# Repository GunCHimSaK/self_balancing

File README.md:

# FOC 정밀 제어 기반 자율주행 밸런싱 로봇

BLDC 모터 2개로 균형을 잡는 2륜 셀프 밸런싱 로봇입니다. 이전 프로젝트([라즈베리파이 자율주행 버스](https://github.com/GunCHimSaK/raspi-autonomous-car))의 차선 인식 주행을 이 로봇에 옮기는 것을 목표로 합니다.
모터는 FOC(Field-Oriented Control)로 토크를 직접 제어해서, DC 모터보다 부드럽고 정밀하게 움직입니다.

- **MCU**: STM32 NUCLEO-F446RE (PlatformIO + Arduino 프레임워크). 처음에는 NUCLEO-F103RB로 시작했습니다.
- **IMU**: BNO055 (MPU6050에서 교체)
- **상위 제어기**: Raspberry Pi 4B (카메라 비전, 주행 명령)
- **통신**: CAN (Raspberry Pi MCP2515 HAT ↔ STM32 TJA1050)
- **기간**: 2025.06 ~ 2026.02

## 시스템 구조

```
[Raspberry Pi 4B]  카메라 → 차선 인식 → throttle / steer
        │  CAN 500kbps (MCP2515 HAT ↔ TJA1050), ID 0x100
        ▼
[STM32 NUCLEO-F446RE]
   BNO055 (I2C1) ──▶ 현재 기울기 ──────────────┐
   AS5048A ×2 (SPI1/SPI2) ──▶ 바퀴 속도 ──▶ 속도 PID ──▶ 목표 기울기
                                               ▼
                                     기울기 PID ──▶ 토크 명령 ± steering
                                               ▼
                               SimpleFOC 토크 제어 (FOC)
        ├─ SimpleFOC Shield A → GM4108 모터 A
        └─ SimpleFOC Shield B → GM4108 모터 B
```

## 제어 구조

**1. FOC 토크 제어 (SimpleFOC)**
- 모터: GM4108 (11 pole pairs), 전원 설정 10V
- 제어 모드: `MotionControlType::torque` (전압 기반 토크 제어)
- 회전자 각도: AS5048A 14bit 자기 엔코더 (SPI 500kHz, 저수준 직접 읽기)

**2. 캐스케이드 밸런싱 제어** (`src/main.cpp`)

```
바퀴 평균 속도 = (모터1 속도 + 모터2 속도) / 2
목표 기울기 = LPF( pid_vel(바퀴 평균 속도 − LPF(throttle)) ) + 0.045      ← 바깥 루프 (속도)
토크 명령   = −pid_stb(목표 기울기 − 현재 기울기)                         ← 안쪽 루프 (기울기)
모터1 = 토크 명령 + LPF(steering),  모터2 = 토크 명령 − LPF(steering)
```

| 제어기 | P | I | D | 출력 제한 |
|---|---|---|---|---|
| `pid_stb` (기울기 → 토크) | 30 | 100 | 1 | 8V |
| `pid_vel` (속도 → 목표 기울기) | 0.01 | 0.03 | 0 | π/10 rad |

- 속도 루프가 로봇이 한쪽으로 굴러가는 것을 막고, `throttle`을 주면 그 속도로 움직입니다.
- `+0.045 rad`는 무게중심이 치우친 만큼의 보정값입니다.
- 시리얼 Commander로 PID 실시간 튜닝 (`A` = 기울기 PID, `B` = 속도 PID)

**3. 자세 추정 (BNO055)**
- 칩 안에서 9축 센서 퓨전을 하는 BNO055의 Euler pitch 레지스터(`0x1E`)를 2바이트 직접 읽습니다 (1° = 16 LSB).
- I2C1(PB8/PB9) 400kHz

| 버전 | 방식 | 결과 |
|---|---|---|
| MPU6050 + 상보 필터 | 레지스터 직접 읽기(burst read) + 가속도 LPF + 상보 필터 | 급격한 기울기에서 멈춤 |
| MPU6050 DMP | DMP 쿼터니언으로 pitch 계산 | 튜닝 성공, 그러나 한 방향 drift |
| **BNO055** | 9축 센서 퓨전 결과 직접 읽기 | drift 해결 (최종) |

**4. CAN 통신** (단독 테스트 완료, 밸런싱 코드와 통합 예정)
- STM32 CAN을 HAL로 직접 초기화한 수신 테스트 (500kbps, F103RB)
- 메시지 `0x100`: `throttle×1000`, `steer×1000`을 big-endian int16 2개로 전송

코드가 단계별로 어떻게 바뀌었는지는 [docs/DEVELOPMENT_LOG.md](docs/DEVELOPMENT_LOG.md)에 정리했습니다.

## 폴더 구조

```
├── src/main.cpp                  밸런싱 메인 펌웨어 (최종: F446RE, BNO055, 캐스케이드 PID)
├── lib/MySensors/
│   ├── balancer_pinouts.h        핀 정의
│   ├── CustomAS5048A.*           AS5048A SPI 저수준 드라이버 (SimpleFOC Sensor 상속)
│   ├── MPU6050_Handler.*         MPU6050 레지스터 + 상보 필터
│   └── mpu6050v2.*               MPU6050 DMP
├── versions/                     단계별 이전 코드 (v1 MPU6050, v2 CAN 수신, v3 BNO055)
├── raspberry_pi/can_sender.py    라즈베리파이 CAN 송신 테스트 (python-can)
├── hardware/
│   ├── cubemx/                   핀 할당 전용 CubeMX 파일 (F446RE, F103RB)
│   └── interface_pcb/            전원·버튼 인터페이스 PCB (KiCad, 거버, BOM)
├── docs/PINMAP.md                전체 핀맵과 핀 충돌 정리
├── docs/DEVELOPMENT_LOG.md       단계별 코드 변화 기록
└── platformio.ini
```

## 핀맵 요약

| 기능 | 모터 A | 모터 B |
|---|---|---|
| 엔코더 SPI (SCK/MISO/MOSI/CS) | SPI1: PA5 / PA6 / PA7 / PB5 | SPI2: PB13 / PB14 / PB15 / PB2 |
| PWM A/B/C상 | PB10 (TIM2) / PB6 (TIM4) / PB4 (TIM3) | PA8 / PA9 / PA10 (TIM1) |
| Enable | PC7 | PA11 (`.ioc`에서는 PC8) |

| 기능 | 핀 |
|---|---|
| I2C1 (BNO055, LCD) | PB8 SCL / PB9 SDA |
| CAN | PA11 RX / PA12 TX (`.ioc` 기준) |
| 디버그 UART | PA2 / PA3 (USART2, ST-LINK) |

자세한 내용과 핀 충돌 정리는 [docs/PINMAP.md](docs/PINMAP.md)에 있습니다.

## 빌드

```bash
pio run -t upload          # 밸런싱 펌웨어 업로드
pio device monitor         # 115200bps, Commander로 PID 튜닝
```
CAN 수신 테스트는 `versions/v2_can_receiver_hal_f103rb.cpp`를 `src/main.cpp`로 바꾸고, `platformio.ini`의 보드를 `nucleo_f103rb`로 바꿔 빌드합니다.
라즈베리파이 쪽은 `sudo ip link set can0 up type can bitrate 500000` 후 `python3 raspberry_pi/can_sender.py`를 실행합니다.

## 개발 중 문제와 해결

| 문제 | 원인 | 해결 |
|---|---|---|
| SimpleFOC에서 AS5048A 값이 안 읽힘 | 원인을 찾지 못함 (라이브러리 기본 SPI 센서 클래스 문제로 추정) | SPI를 직접 읽는 `CustomAS5048A` 클래스를 만들어 SimpleFOC `Sensor`로 연결 |
| 모터 2개를 동시에 못 돌림 | 두 쉴드의 PWM 핀이 같은 타이머를 사용 | PWM 선을 끊고 타이머가 겹치지 않는 핀(모터 B → TIM1)으로 다시 납땜 |
| 모터 1개 고장 | 모터 규격보다 긴 나사가 내부 코일을 끊음 | 모터 교체, 나사 길이 확인 |
| 급격히 기울이면 로봇이 멈춤 | IMU 통신 중 멈춤 | burst read로 I2C 통신 횟수를 줄이고, DMP 방식으로 변경 |
| 각도가 한 방향으로 흘러감 (drift) | 6축 센서 한계 또는 센서 불량 | BNO055 9축 센서로 교체 |
| 엔코더 값 불안정 | SPI 속도와 CS 타이밍 | SPI 1MHz → 500kHz, CS를 내린 뒤 1µs 대기 |
| 제자리에 서지 못하고 굴러감 | 기울기만 제어 | 바퀴 속도 루프를 바깥에 둔 캐스케이드 PID |
| 디커플링 커패시터가 제 역할을 못 함 (PCB) | 100µF 커패시터를 전원–GND 사이가 아니라 12V 라인에 직렬로 배치 | 2차 설계에서 전원–GND 사이, IC 핀 가까이 배치 |
| 센서·버튼 입력값이 튐 (PCB) | 커넥터에 GND 핀이 없어 기준 전위가 공유되지 않음 | GND 선을 따로 연결, 2차 설계에서 모든 신호 커넥터에 GND 핀 추가 |
| CAN과 IMU 핀 충돌 | CAN remap(PB8/PB9)과 I2C1 핀이 같음 | CAN을 PA11/PA12로 옮기는 핀 배치 정리 (`.ioc`) |

## 사용 도구
STM32CubeMX · PlatformIO · VS Code · SimpleFOC · KiCad · Fusion 360

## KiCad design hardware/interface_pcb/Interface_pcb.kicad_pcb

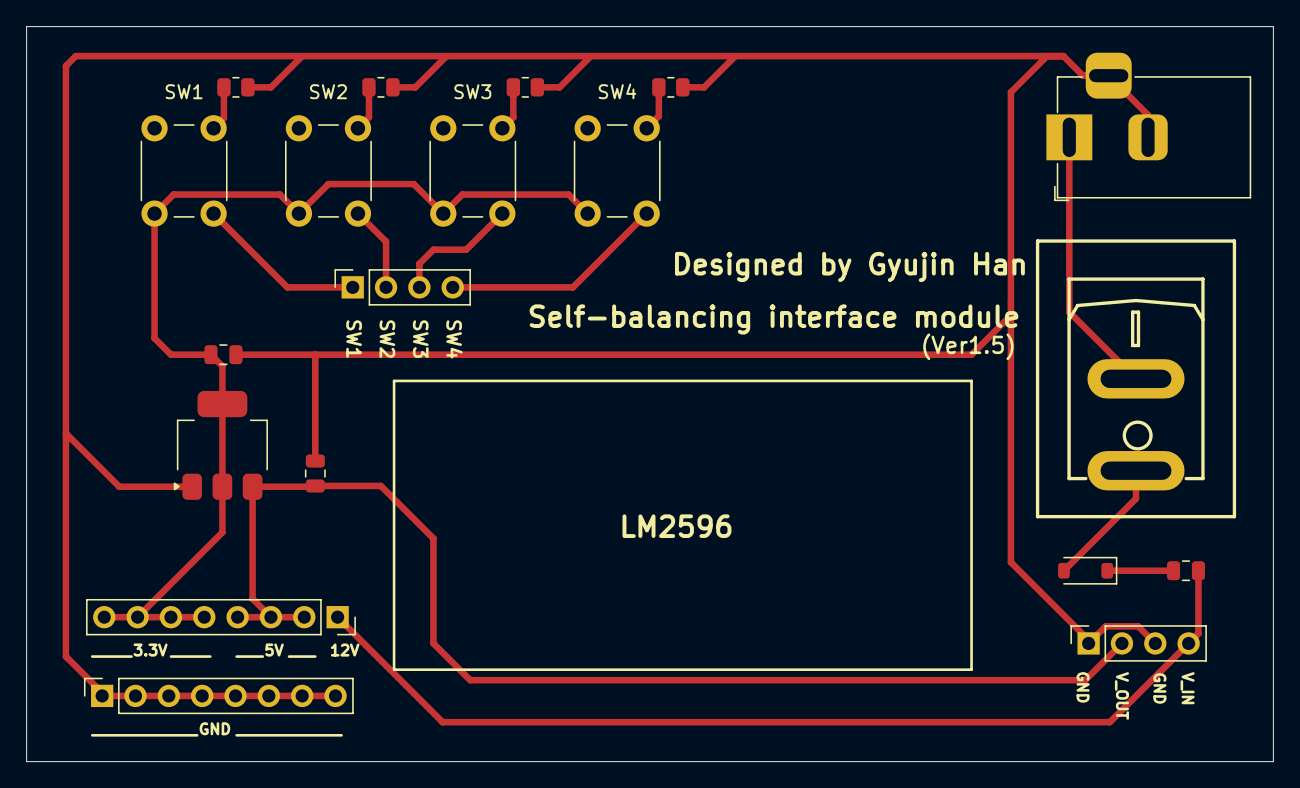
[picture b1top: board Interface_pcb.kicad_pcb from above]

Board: 2 copper layers, 95.0 x 56.0 mm, 19 parts (0 on the bottom side), 11 nets.

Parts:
BT1: 12v; BarrelJack_Horizontal
C1: 10uF; C_0805_2012Metric
C2: 22uF; C_0805_2012Metric
C3: 100uF; C_0805_2012Metric
D1: D; D_SOD-123
J1: Conn_01x04_Socket; PinSocket_1x04_P2.54mm_Vertical
J2: Conn_01x04_Pin; PinSocket_1x04_P2.54mm_Vertical
J4, J6: Conn_01x08_Socket; PinSocket_1x08_P2.54mm_Vertical
R1, R2, R3, R4: 10k; R_0805_2012Metric
SW1, SW2, SW3, SW4: SW_Push; SW_PUSH_6mm
SW1#2: SW_SPST; SW-TH_SS11-BBIWQ-XX
U1: AMS1117-3.3; SOT-223-3_TabPin2

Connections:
unnamed: BT1.1 (+), SW1#2.2 (B)
unnamed: BT1.2 (-), BT1.3, C1.2, C2.2, J1.1, J1.3, J6.1, J6.2, J6.3, J6.4, J6.5, J6.6, J6.7, J6.8, R1.1, R2.1, R3.1, R4.1, U1.1 (GND)
unnamed: D1.2 (A), SW1#2.1 (A)
unnamed: C3.2, D1.1 (K)
unnamed: C1.1, J1.2, J4.2, J4.3, J4.4, U1.3 (VI)
unnamed: C3.1, J1.4, J4.1
unnamed: J2.1, R1.2, SW1.1
unnamed: J2.2, R2.2, SW2.1
unnamed: J2.3, R3.2, SW3.1
unnamed: J2.4, R4.2, SW4.1
unnamed: C2.1, J4.5, J4.6, J4.7, J4.8, SW1.2, SW2.2, SW3.2, SW4.2, U1.2 (VO)

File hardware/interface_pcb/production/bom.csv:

Designator,Footprint,Quantity,Value,LCSC Part #
BT1,BarrelJack_Horizontal,1,12v,
C1,0805,1,10uF,
C2,0805,1,22uF,
C3,0805,1,100uF,
D1,D_SOD-123,1,D,
J1,PinSocket_1x04_P2.54mm_Vertical,1,Conn_01x04_Socket,
J2,PinSocket_1x04_P2.54mm_Vertical,1,Conn_01x04_Pin,
"J4, J6",PinSocket_1x08_P2.54mm_Vertical,2,Conn_01x08_Socket,
"R1, R2, R3, R4",0805,4,10k,
"SW1_2, SW2, SW3, SW4",SW_PUSH_6mm,4,SW_Push,
SW1,SW-TH_SS11-BBIWQ-XX,1,SW_SPST,
U1,SOT-223-3_TabPin2,1,AMS1117-3.3,
